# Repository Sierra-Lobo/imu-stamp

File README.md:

# imu-stamp

9-axis inertial measurement unit with dual sensors for gyro, mag, and accel measurements.

see LTC4317 datasheet for information on setting the I2C addresses of each sensor.

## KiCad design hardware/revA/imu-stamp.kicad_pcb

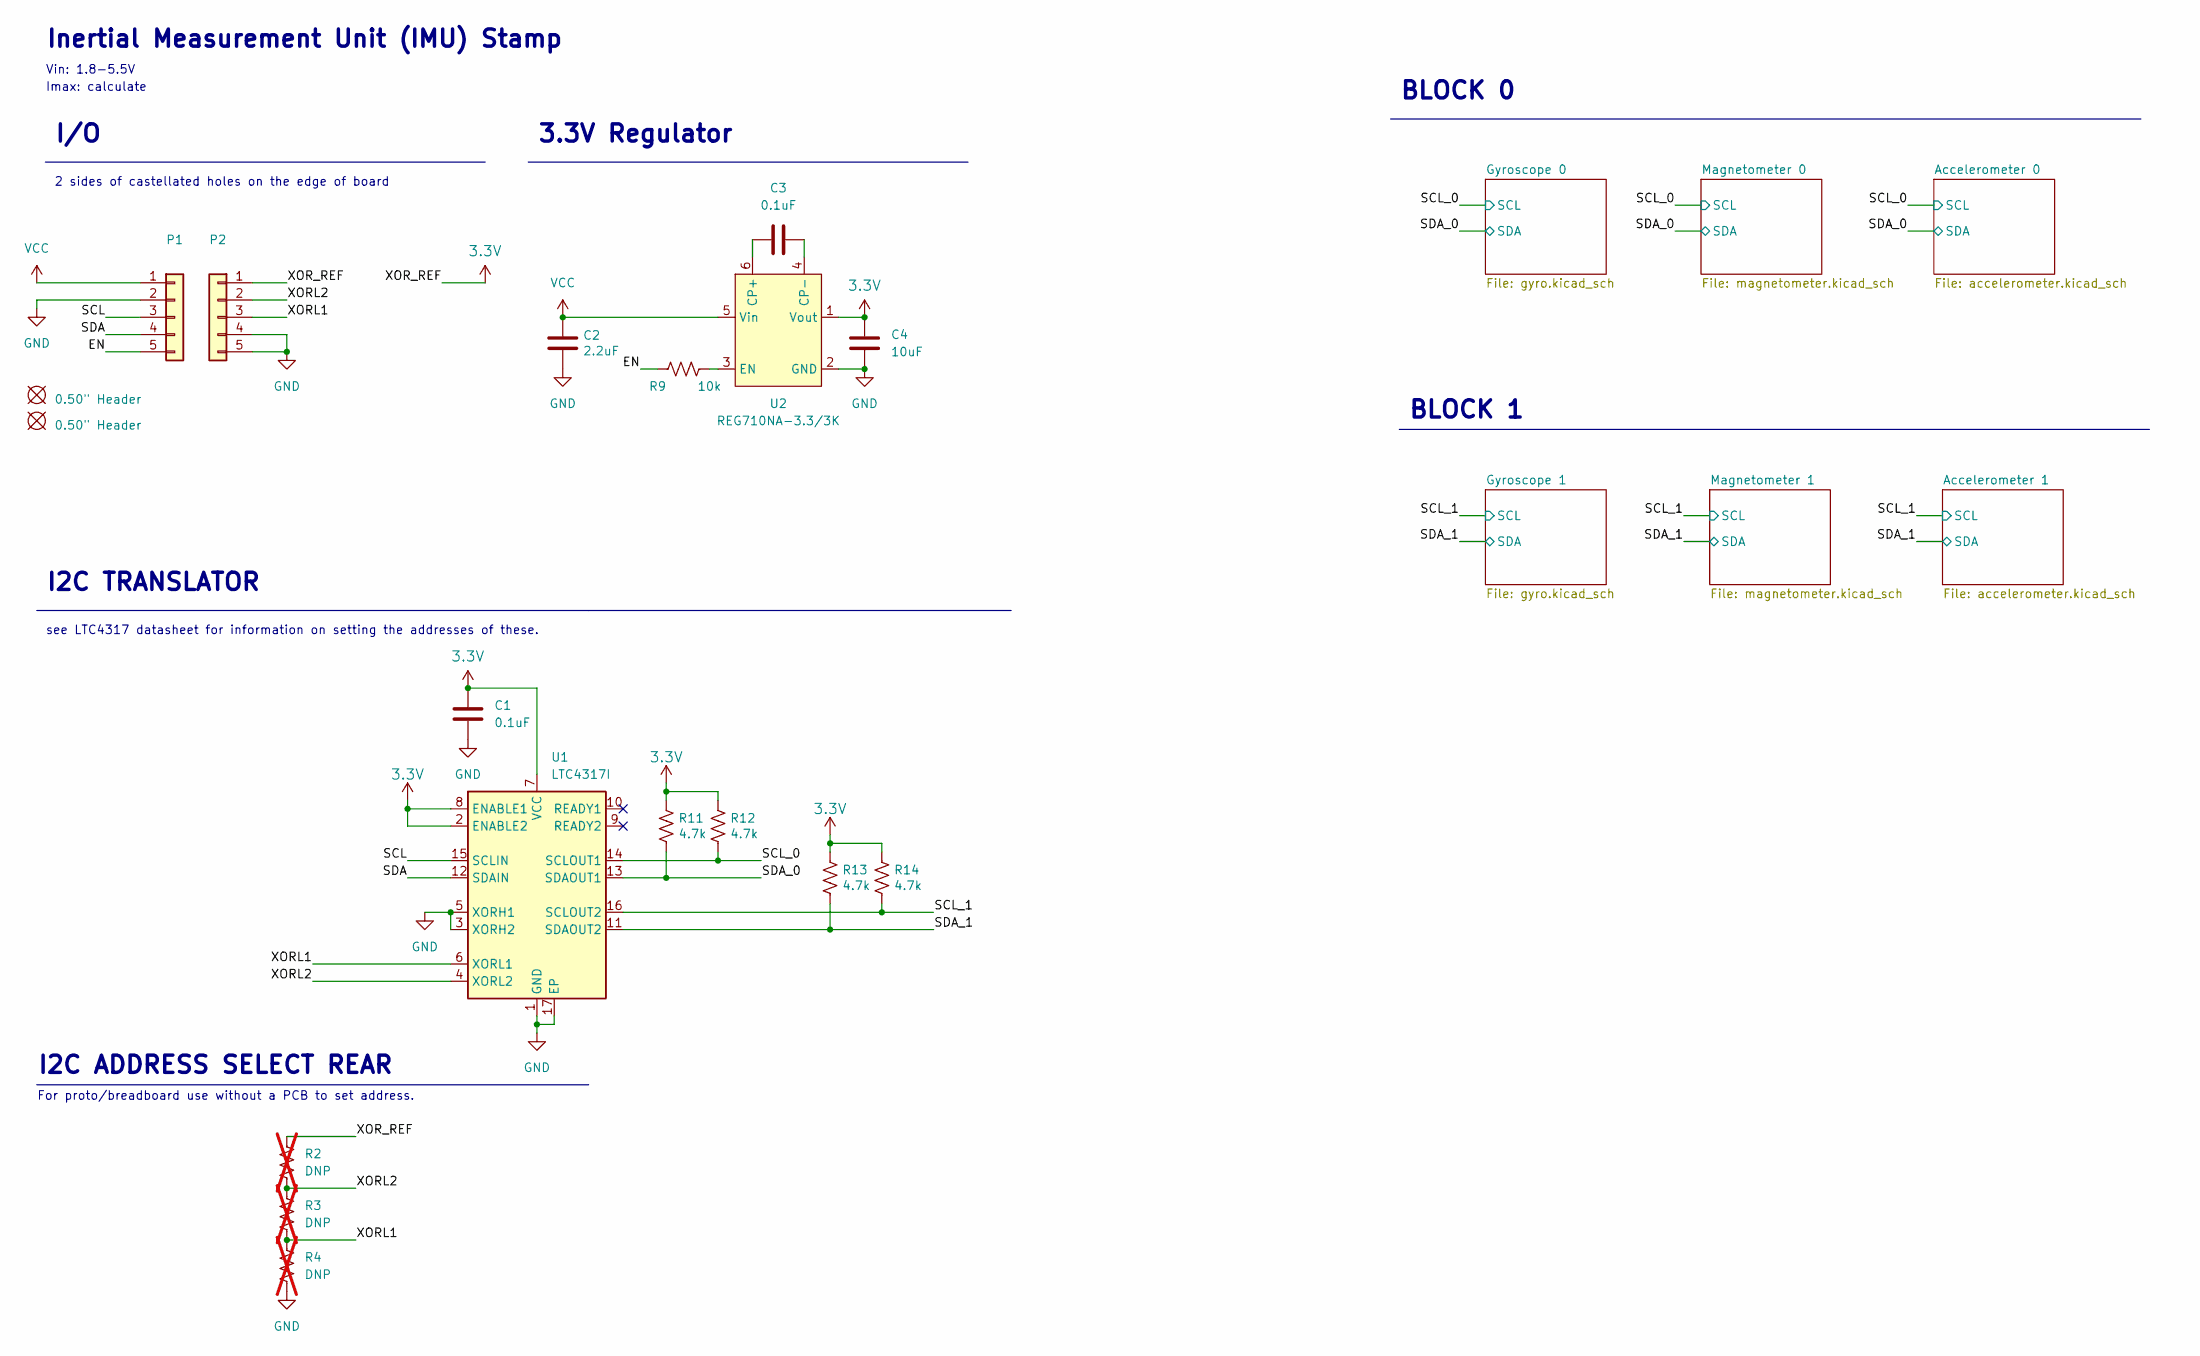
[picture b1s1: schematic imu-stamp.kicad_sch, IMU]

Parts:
BOM1, BOM2: 0.50" Header
C1: 0.1uF; C_0201_0603Metric
C2: 2.2uF; C_0603_1608Metric
C3: 0.1uF; C_0603_1608Metric
C4: 10uF; C_0603_1608Metric
P1, P2: I/O; Castellated_1x05_P1.27mm_Vertical
R2, R3, R4: DNP; R_0402_1005Metric; not fitted
R9: 10k; R_0201_0603Metric
R11, R12, R13, R14: 4.7k; R_0201_0603Metric
U1: LTC4317I; DFN-16-1EP_3x5mm_P0.5mm_EP1.66x4.4mm
U2: REG710NA-3.3/3K; SOT-23-6

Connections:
3.3V: C1.2, C4.1, P2.1, R2.1, R11.1, R12.1, R13.1, R14.1, U1.2 (ENABLE2), U1.7 (VCC), U1.8 (ENABLE1), U2.1 (Vout); also elsewhere on the board
/EN: P1.5, R9.1
/SCL: P1.3, U1.15 (SCLIN)
/SCL_0: R12.2, U1.14 (SCLOUT1); also elsewhere on the board
/SCL_1: R14.2, U1.16 (SCLOUT2); also elsewhere on the board
/SDA: P1.4, U1.12 (SDAIN)
/SDA_0: R11.2, U1.13 (SDAOUT1); also elsewhere on the board
/SDA_1: R13.2, U1.11 (SDAOUT2); also elsewhere on the board
/XORL1: P2.3, R3.2, R4.1, U1.6 (XORL1)
/XORL2: P2.2, R2.2, R3.1, U1.4 (XORL2)
GND: C1.1, C2.2, C4.2, P1.2, P2.4, P2.5, R4.2, U1.1 (GND), U1.3 (XORH2), U1.5 (XORH1), U1.17 (EP), U2.2 (GND); also elsewhere on the board
unnamed: C3.1, U2.6 (CP+)
unnamed: C3.2, U2.4 (CP-)
unnamed: R9.2, U2.3 (EN)
VCC: C2.1, P1.1, U2.5 (Vin)

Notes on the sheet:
I2C TRANSLATOR
2 sides of castellated holes on the edge of board
Imax: calculate
I/O
see LTC4317 datasheet for information on setting the addresses of these.
Inertial Measurement Unit (IMU) Stamp
I2C ADDRESS SELECT REAR
BLOCK 0
BLOCK 1
Vin: 1.8-5.5V
For proto/breadboard use without a PCB to set address.
3.3V Regulator

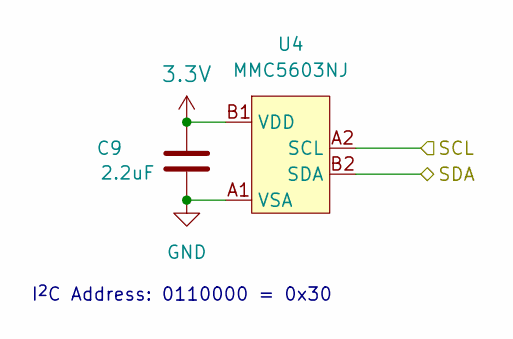
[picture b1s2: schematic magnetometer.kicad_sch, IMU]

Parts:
C9: 2.2uF; C_0402_1005Metric
U4: MMC5603NJ; WLP-4_0.83x0.83mm_P0.4mm

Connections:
3.3V: C9.1, U4.B1 (VDD); also elsewhere on the board
/SCL_0: U4.A2 (SCL); also elsewhere on the board
/SDA_0: U4.B2 (SDA); also elsewhere on the board
GND: C9.2, U4.A1 (VSA); also elsewhere on the board

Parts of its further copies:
C15: 2.2uF; C_0402_1005Metric
U7: MMC5603NJ; WLP-4_0.83x0.83mm_P0.4mm

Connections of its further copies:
3.3V: C15.1, U7.B1 (VDD); also elsewhere on the board
/SCL_1: U7.A2 (SCL); also elsewhere on the board
/SDA_1: U7.B2 (SDA); also elsewhere on the board
GND: C15.2, U7.A1 (VSA); also elsewhere on the board

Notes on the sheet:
I^{2}C Address: 0110000 = 0x30

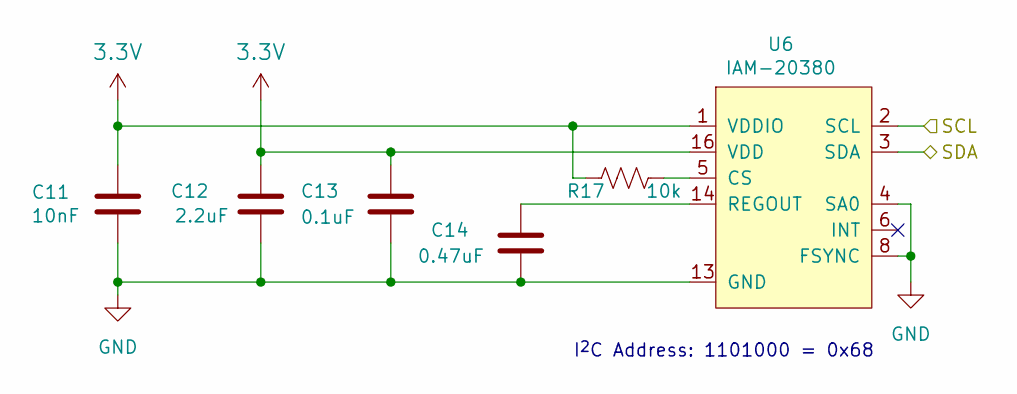
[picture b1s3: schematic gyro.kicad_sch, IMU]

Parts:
C11: 10nF; C_0201_0603Metric
C12: 2.2uF; C_0402_1005Metric
C13: 0.1uF; C_0201_0603Metric
C14: 0.47uF; C_0201_0603Metric
R17: 10k; R_0201_0603Metric
U6: IAM-20380; LGA-16_3x3mm_P0.5mm_LayoutBorder3x5y

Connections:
3.3V: C11.1, C12.1, C13.2, R17.1, U6.1 (VDDIO), U6.16 (VDD); also elsewhere on the board
/SCL_0: U6.2 (SCL); also elsewhere on the board
/SDA_0: U6.3 (SDA); also elsewhere on the board
GND: C11.2, C12.2, C13.1, C14.2, U6.4 (SA0), U6.8 (FSYNC), U6.9 (RESV_GND), U6.10 (RESV_GND), U6.11 (RESV_GND), U6.12 (RESV_GND), U6.13 (GND), U6.15 (RESV_GND); also elsewhere on the board
unnamed: R17.2, U6.5 (CS)
unnamed: C14.1, U6.14 (REGOUT)

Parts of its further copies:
C5: 10nF; C_0201_0603Metric
C6: 2.2uF; C_0402_1005Metric
C7: 0.1uF; C_0201_0603Metric
C8: 0.47uF; C_0201_0603Metric
R15: 10k; R_0201_0603Metric
U3: IAM-20380; LGA-16_3x3mm_P0.5mm_LayoutBorder3x5y

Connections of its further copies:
3.3V: C5.1, C6.1, C7.2, R15.1, U3.1 (VDDIO), U3.16 (VDD); also elsewhere on the board
/SCL_1: U3.2 (SCL); also elsewhere on the board
/SDA_1: U3.3 (SDA); also elsewhere on the board
GND: C5.2, C6.2, C7.1, C8.2, U3.4 (SA0), U3.8 (FSYNC), U3.9 (RESV_GND), U3.10 (RESV_GND), U3.11 (RESV_GND), U3.12 (RESV_GND), U3.13 (GND), U3.15 (RESV_GND); also elsewhere on the board
unnamed: R15.2, U3.5 (CS)
unnamed: C8.1, U3.14 (REGOUT)

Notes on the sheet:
I^{2}C Address: 1101000 = 0x68

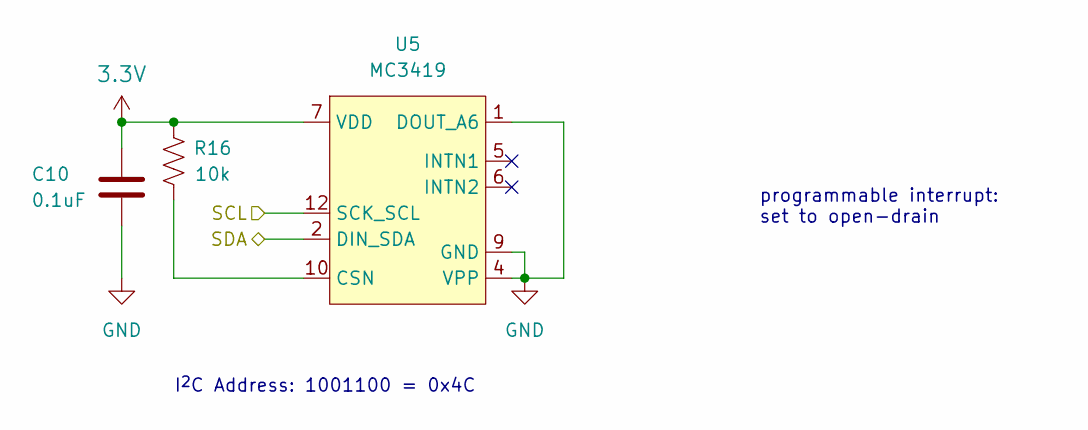
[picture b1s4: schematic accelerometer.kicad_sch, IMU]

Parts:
C10: 0.1uF; C_0201_0603Metric
R16: 10k; R_0201_0603Metric
U5: MC3419; LGA-12_2x2mm_P0.5mm

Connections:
3.3V: C10.2, R16.2, U5.7 (VDD); also elsewhere on the board
/SCL_0: U5.12 (SCK_SCL); also elsewhere on the board
/SDA_0: U5.2 (DIN_SDA); also elsewhere on the board
GND: C10.1, U5.1 (DOUT_A6), U5.4 (VPP), U5.9 (GND); also elsewhere on the board
unnamed: R16.1, U5.10 (CSN)

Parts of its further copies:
C16: 0.1uF; C_0201_0603Metric
R18: 10k; R_0201_0603Metric
U8: MC3419; LGA-12_2x2mm_P0.5mm

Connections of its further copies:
3.3V: C16.2, R18.2, U8.7 (VDD); also elsewhere on the board
/SCL_1: U8.12 (SCK_SCL); also elsewhere on the board
/SDA_1: U8.2 (DIN_SDA); also elsewhere on the board
GND: C16.1, U8.1 (DOUT_A6), U8.4 (VPP), U8.9 (GND); also elsewhere on the board
unnamed: R18.1, U8.10 (CSN)

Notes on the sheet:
I^{2}C Address: 1001100 = 0x4C
programmable interrupt: set to open-drain

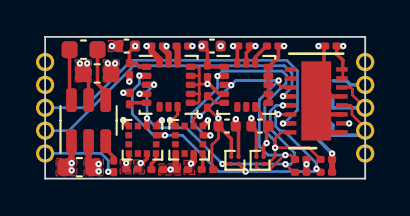
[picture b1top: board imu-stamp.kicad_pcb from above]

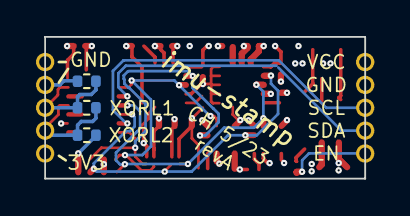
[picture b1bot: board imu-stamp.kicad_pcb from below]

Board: 4 copper layers, 17.8 x 7.9 mm, 38 parts (3 on the bottom side), 21 nets.

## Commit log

2023-03-03 added submodules
2023-03-03 removed extra folder
2023-03-03 modules
2023-03-07 updated iam20380 footprint
    to exclude solder mask per AN-IVS-0002A-00
2023-03-12 Update SierraLobo_CircuitPython_IAM20380
2023-03-12 Update SierraLobo_CircuitPython_MC3419
2023-03-13 editing submodule links
2023-03-13 updated submodule path, added symbolic links to /software for easy python integration
2023-03-13 removed failed symlink
2023-03-13 updated iam20380 submodule
2023-03-14 Update Adafruit_CircuitPython_MMC56x3
2023-03-14 update sierralobo IAM20380 & MC3419
2023-03-14 adjusted castellated hole size and position
2023-03-20 remove Thumbs.db
2023-03-22 moved software to a different repo
2023-05-23 consistency updates
2023-06-05 resized board for manufacturing
2023-07-05 added p/n to drawing sheet
